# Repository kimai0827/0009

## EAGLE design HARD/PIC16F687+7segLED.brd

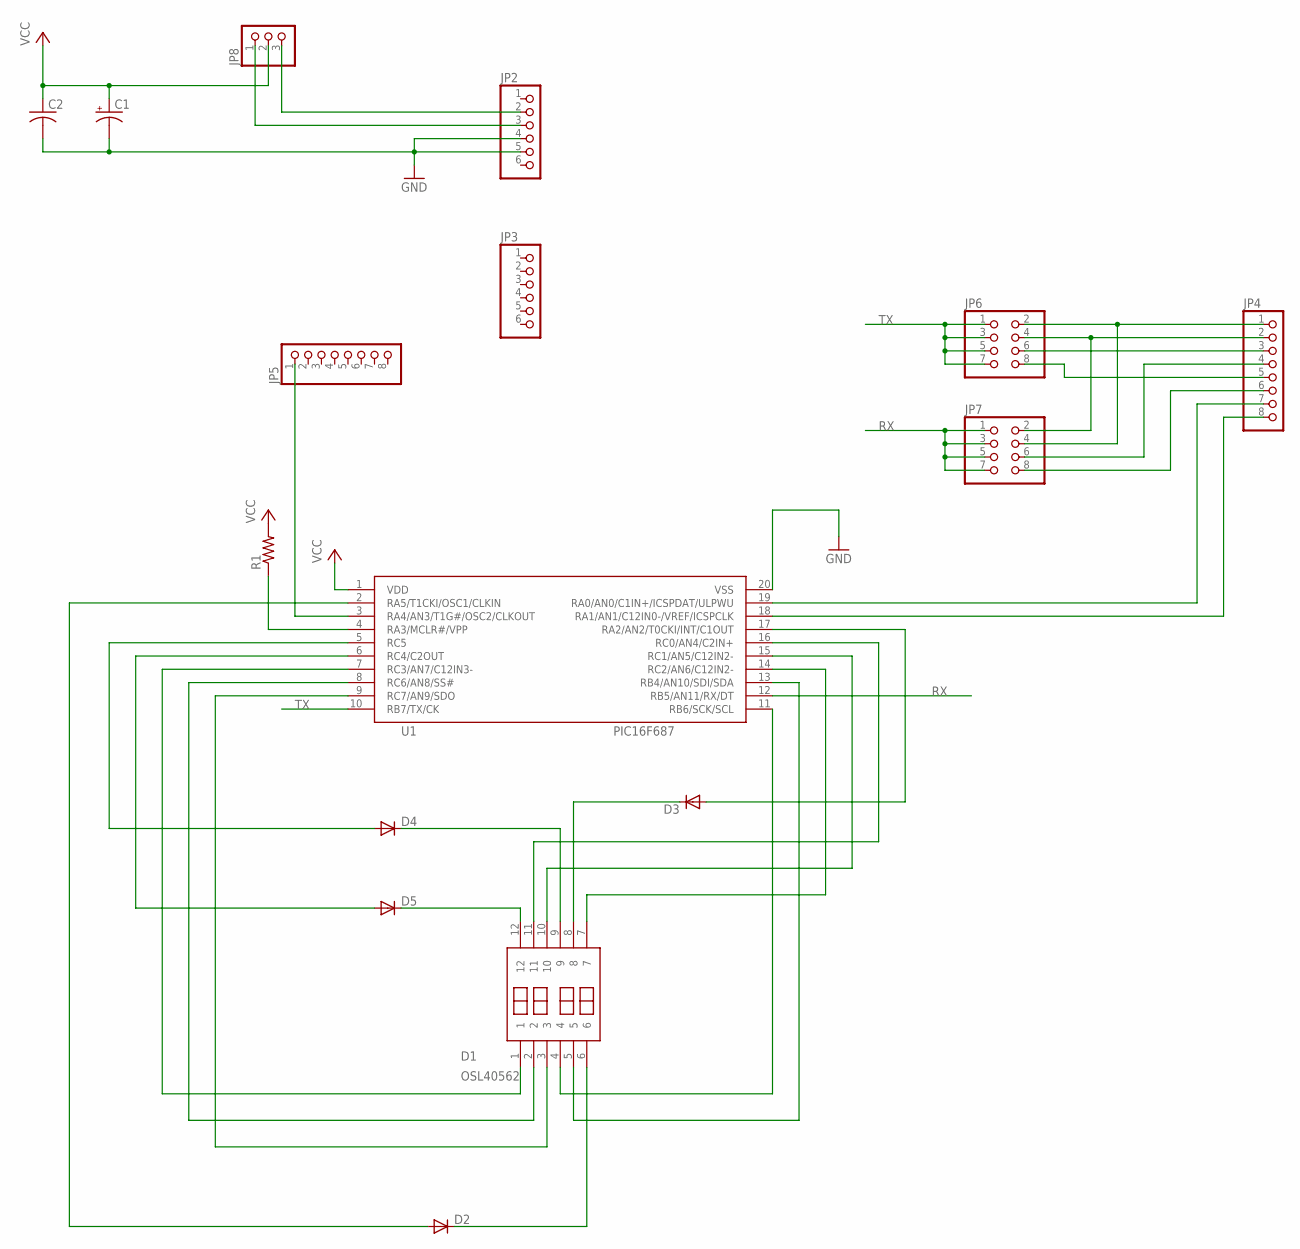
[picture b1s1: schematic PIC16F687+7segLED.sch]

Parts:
C1: CPOL-US
C2: CAP; C025-040X050
D1: OSL40562
D2, D3, D4, D5: DIODE-01; 0204_D
JP2, JP3: PINHD-1X6; 1X06
JP4, JP5: PINHD-1X8; 1X08
JP6, JP7: PINHD-2X4; 2X04
JP8: PINHD-1X3; 1X03
R1: R-US-01; 0204V
U1: PIC16F687; DIP20

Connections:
GND: C1.-, C2.2, JP2.4, JP2.5, U1.20 (VSS)
unnamed: D4.1 (A), U1.5 (RC5)
unnamed: D2.1 (A), U1.2 (RA5/T1CKI/OSC1/CLKIN)
unnamed: D5.1 (A), U1.6 (RC4/C2OUT)
unnamed: D1.1, U1.7 (RC3/AN7/C12IN3-)
unnamed: D1.2, U1.8 (RC6/AN8/SS#)
unnamed: D1.3, U1.9 (RC7/AN9/SDO)
unnamed: D1.4, U1.11 (RB6/SCK/SCL)
unnamed: D1.5, U1.13 (RB4/AN10/SDI/SDA)
unnamed: D1.7, U1.14 (RC2/AN6/C12IN2-)
unnamed: D1.10, U1.15 (RC1/AN5/C12IN2-)
unnamed: D1.11, U1.16 (RC0/AN4/C2IN+)
unnamed: D3.1 (A), U1.17 (RA2/AN2/T0CKI/INT/C1OUT)
unnamed: D1.6, D2.2 (C)
unnamed: D1.8, D3.2 (C)
unnamed: D1.9, D4.2 (C)
unnamed: D1.12, D5.2 (C)
unnamed: R1.1, U1.4 (RA3/MCLR#/VPP)
unnamed: JP4.7, U1.19 (RA0/AN0/C1IN+/ICSPDAT/ULPWU)
unnamed: JP4.8, U1.18 (RA1/AN1/C12IN0-/VREF/ICSPCLK)
unnamed: JP5.1, U1.3 (RA4/AN3/T1G#/OSC2/CLKOUT)
unnamed: JP4.1, JP6.2, JP7.4
unnamed: JP4.2, JP6.4, JP7.2
unnamed: JP4.3, JP6.6
unnamed: JP4.5, JP6.8
unnamed: JP2.2, JP8.3
unnamed: JP2.3, JP8.1
unnamed: JP4.4, JP7.6
unnamed: JP4.6, JP7.8
RX: JP7.1, JP7.3, JP7.5, JP7.7, U1.12 (RB5/AN11/RX/DT)
TX: JP6.1, JP6.3, JP6.5, JP6.7, U1.10 (RB7/TX/CK)
VCC: C1.+, C2.1, JP8.2, R1.2, U1.1 (VDD)

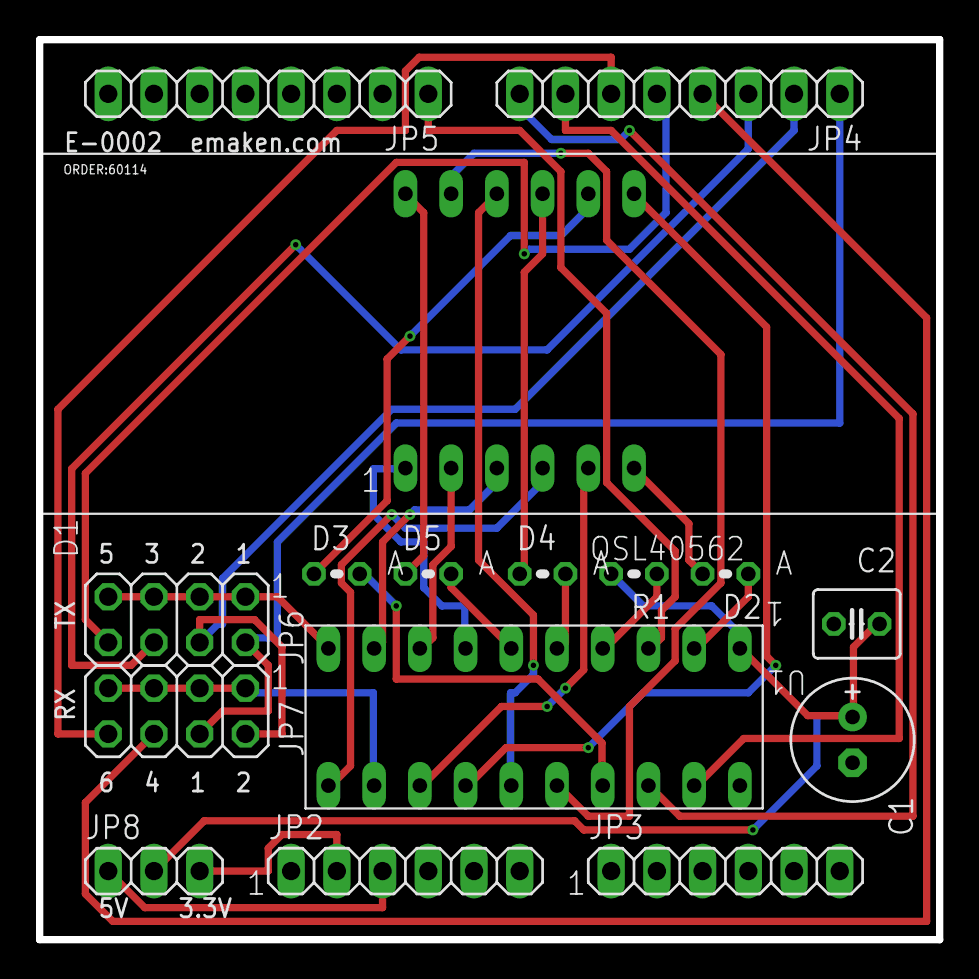
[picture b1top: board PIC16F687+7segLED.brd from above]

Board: 2 copper layers, 50.0 x 50.0 mm, 16 parts (0 on the bottom side), 32 nets.

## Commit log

2012-11-06 initial release
